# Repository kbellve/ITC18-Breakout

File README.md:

<p>This board was codeveloped by Joseph Bellve and Kishore Rao as a student Summer project.</p>

<p>The purpose of the board is to allow the use of either:</p>

<p>ITC18 Bottom 50 pin Connector:</p>
	
	TTL outputs 4-7 and TTL Inputs 4-7

<p>ITC18 Top 50 pin Connector:</p>

	TTL Outputs 8 - 15 sent to a parallel connector to control a Sutter 10-2 filter wheel.

	or 

	TTL Outputs 12-15 sent to BNC
	TTL Inputs 12-15 sent to BNC

BOM: http://www.mouser.com/ProjectManager/ProjectDetail.aspx?AccessID=0ec57dda47 "Mouser"

<p>Karl Bellve</p>
<p>Biomedical Imaging Group</p>
<p>Molecular Medicine</p>
<p>University of Massachusetts Medical School</p>

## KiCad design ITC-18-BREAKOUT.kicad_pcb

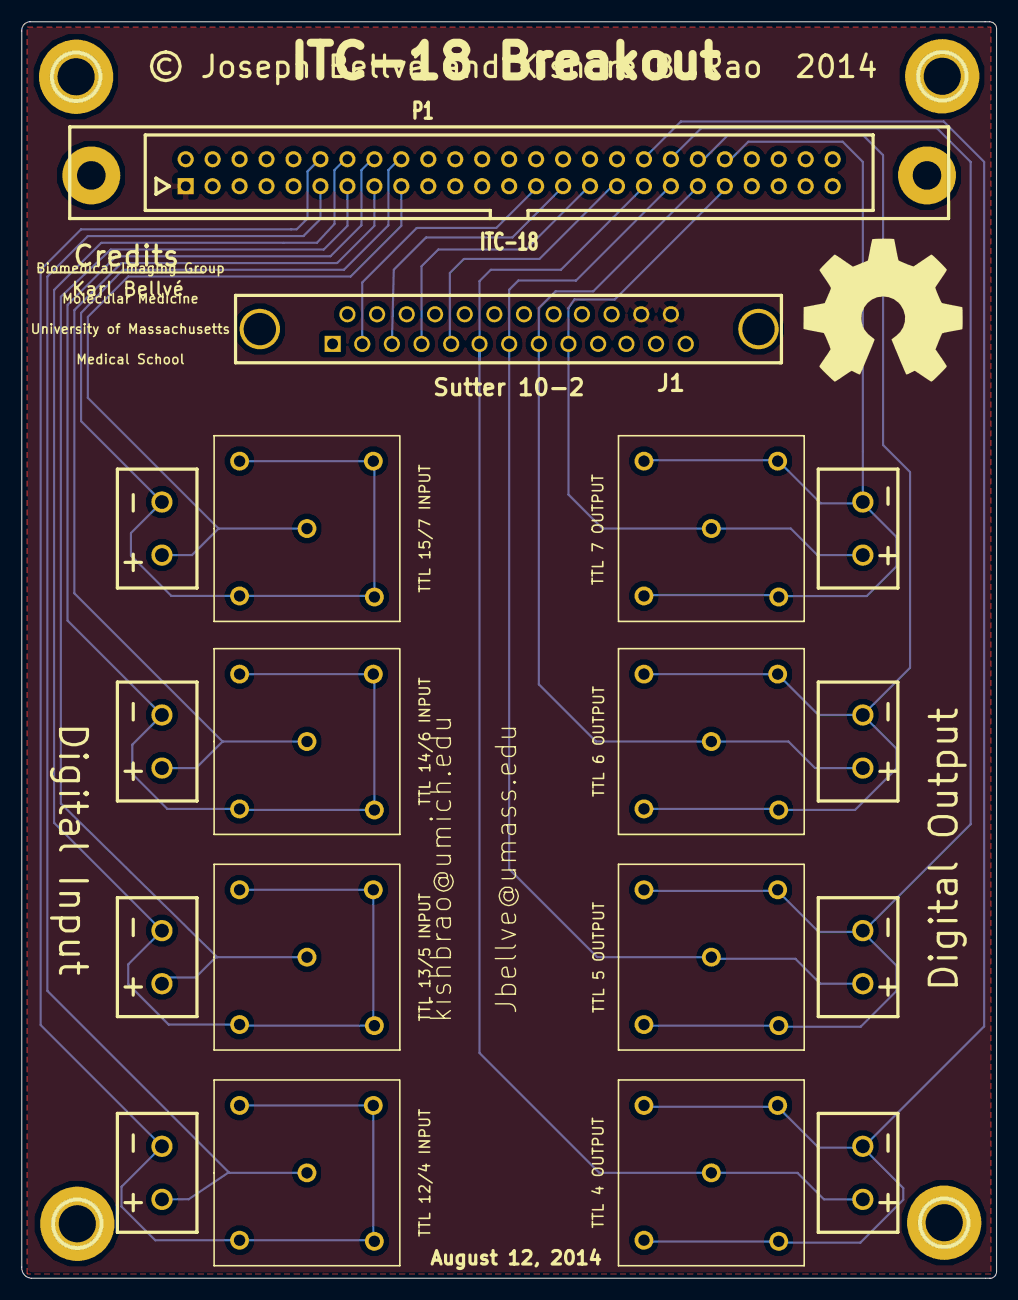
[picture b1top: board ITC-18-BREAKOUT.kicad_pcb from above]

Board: 2 copper layers, 91.8 x 118.4 mm, 22 parts (0 on the bottom side), 21 nets.

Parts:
J1: Sutter 10-2; DB25FD
P1: ITC-18; HE10_50D
P2: TTL 0; C2_5mm
P3: 3; C2_5mm
P4: TTL 15/7 INPUT; BNC-S
P5: TTL 7 OUTPUT; BNC-S
P6: TTL 1; C2_5mm
P7: 7; C2_5mm
P8: TTL 14/6 INPUT; BNC-S
P9: TTL 6 OUTPUT; BNC-S
P10: TTL 2; C2_5mm
P11: TTL 5; C2_5mm
P12: TTL 13/5 INPUT; BNC-S
P13: TTL 5 OUTPUT; BNC-S
P14: TTL 3; C2_5mm
P15: TTL 4; C2_5mm
P16: TTL 12/4 INPUT; BNC-S
P17: TTL 4 OUTPUT; BNC-S
P18, P19, P20, P21: CONN_1; 3.5_MM_DRILLHOLE

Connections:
/11: P1.11, P14.1, P16.1
/12: P1.12, P14.2, P16.2
/13: P1.13, P10.1, P12.1
/14: P1.14, P10.2, P12.2
/15: P1.15, P6.1, P8.1
/16: P1.16, P6.2, P8.2
/17: P1.17, P2.1, P4.1
/18: P1.18, P2.2, P4.2
/27-2: J1.2, P1.27
/29-3: J1.3, P1.29
/31-4: J1.4, P1.31
/33-5: J1.5, P1.33
/35-6: J1.6, P1.35, P15.1, P17.1
/37-7: J1.7, P1.37, P11.1, P13.1
/39-8: J1.8, P1.39, P7.1, P9.1
/41-9: J1.9, P1.41, P3.1, P5.1
/42-GND: P1.42, P3.2, P5.2
GND: J1.24, J1.25, P1.1
unnamed: P1.40, P7.2, P9.2
unnamed: P1.36, P15.2, P17.2
unnamed: P1.38, P11.2, P13.2

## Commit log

2014-08-12 adding netlist,board and schematic

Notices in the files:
ITC-18-BREAKOUT.kicad_pcb:
© Joseph Bellvé and Kishore B. Rao  2014
